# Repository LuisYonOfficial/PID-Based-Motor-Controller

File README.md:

# PID-Based-Motor-Controller
Feedback controlled 3 phase BLDC motor controller. Hardware and all required files will be hosted here. Repo currently under construction!

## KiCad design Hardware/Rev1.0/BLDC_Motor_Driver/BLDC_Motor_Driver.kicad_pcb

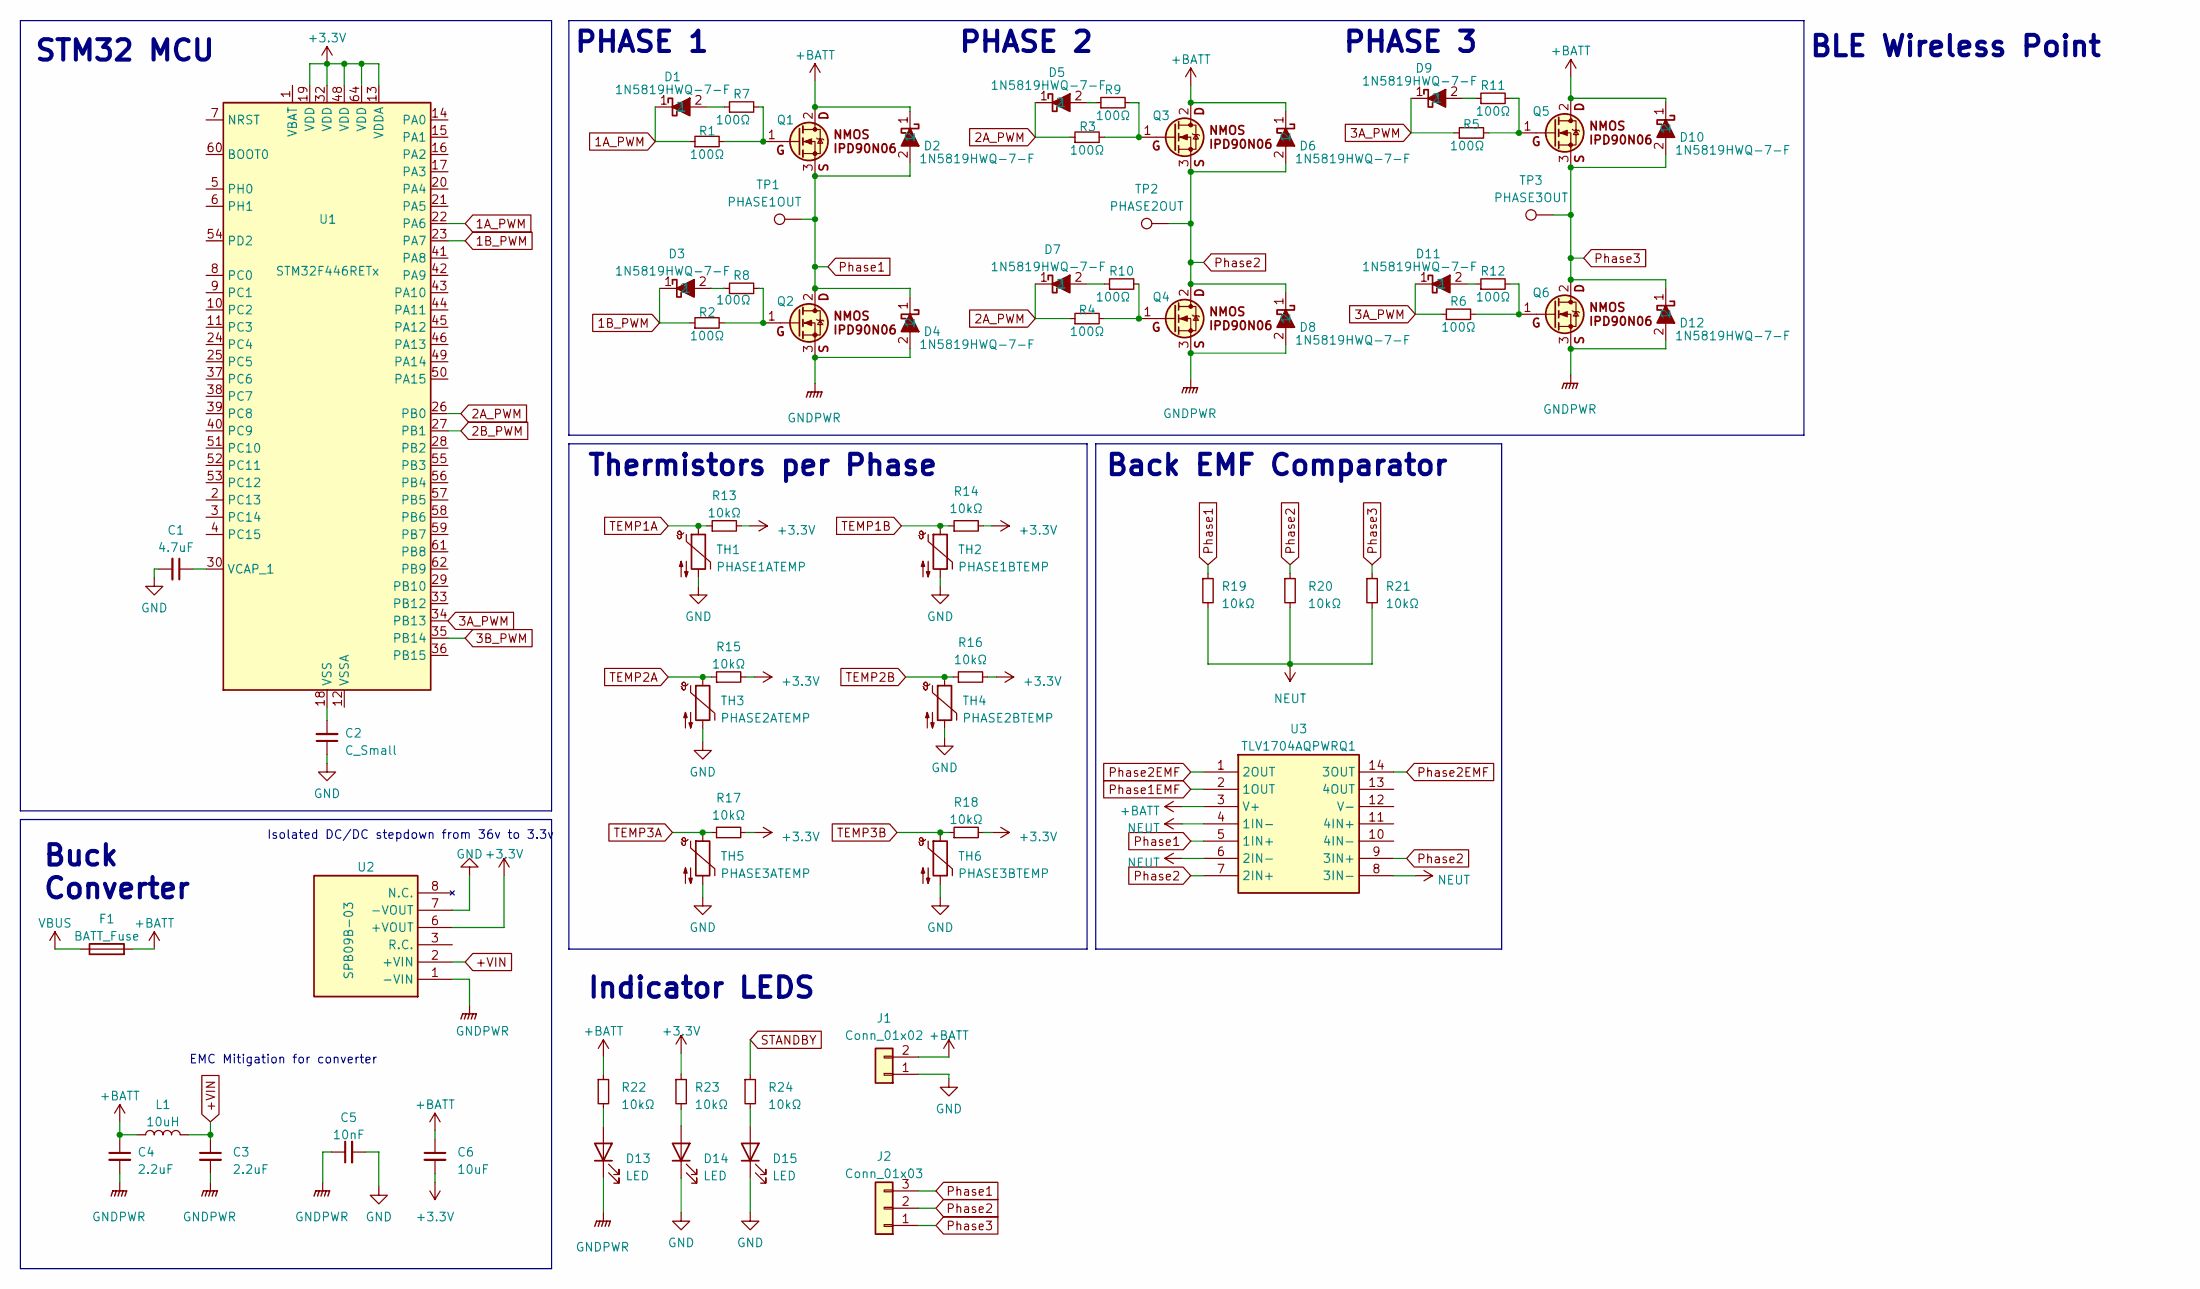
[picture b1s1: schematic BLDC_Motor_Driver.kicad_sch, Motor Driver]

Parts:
C1: 4.7uF; C_0603_1608Metric
C2: C_Small; C_0603_1608Metric
C3, C4: 2.2uF; C_0603_1608Metric
C5: 10nF; C_0603_1608Metric
C6: 10uF; C_0603_1608Metric
D1, D2, D3, D4, D5, D6, D7, D8, D9, D10, D11, D12: 1N5819HWQ-7-F; SOD3716X145N; Mouser Part Number 621-1N5819HWQ-7-F
D13, D14, D15: LED; LED_0603_1608Metric
F1: BATT_Fuse; 3557-2
J1: Conn_01x02
J2: Conn_01x03
L1: 10uH; SRP06152R2K
Q1, Q2, Q3, Q4, Q5, Q6: IPD90N06S4L03ATMA2; IPD90N06S4L03
R1, R2, R3, R4, R5, R6, R7, R8, R9, R10, R11, R12: 100Ω; R_0603_1608Metric
R13, R14, R15, R16, R17, R18, R19, R20, R21, R22, R23, R24: 10kΩ; R_0603_1608Metric
TH1: PHASE1ATEMP; R_0603_1608Metric
TH2: PHASE1BTEMP; R_0603_1608Metric
TH3: PHASE2ATEMP; R_0603_1608Metric
TH4: PHASE2BTEMP; R_0603_1608Metric
TH5: PHASE3ATEMP; R_0603_1608Metric
TH6: PHASE3BTEMP; R_0603_1608Metric
TP1: PHASE1OUT
TP2: PHASE2OUT
TP3: PHASE3OUT
U1: STM32F446RETx; LQFP-64_10x10mm_P0.5mm
U2: SPB09B-03; SPB09B; Mouser Part Number 709-SPB09B-03
U3: TLV1704AQPWRQ1; SOP65P640X120-14N; Mouser Part Number 595-TLV1704AQPWRQ1

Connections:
1A_PWM: D1.1, R1.1, U1.22 (PA6)
1B_PWM: D3.1, R2.1, U1.23 (PA7)
2A_PWM: D5.1, D7.1, R3.1, R4.1, U1.26 (PB0)
2B_PWM: U1.27 (PB1)
3A_PWM: D9.1, D11.1, R5.1, R6.1, U1.34 (PB13)
3B_PWM: U1.35 (PB14)
+3.3V: C6.2, R13.2, R14.2, R15.2, R16.2, R17.2, R18.2, R23.1, U1.13 (VDDA), U1.19 (VDD), U1.32 (VDD), U1.48 (VDD), U1.64 (VDD), U2.6 (+VOUT)
+BATT: C4.1, C6.1, D2.1, D6.1, D10.1, F1.2, J1.2, L1.1, Q1.2, Q3.2, Q5.2, R22.1, U3.3 (V+)
+VIN: C3.1, L1.2, U2.2 (+VIN)
GND: C1.2, C2.1, C5.2, D14.1 (K), D15.1 (K), J1.1, TH1.2, TH2.2, TH3.2, TH4.2, TH5.2, TH6.2, U2.7 (-VOUT)
GNDPWR: C3.2, C4.2, C5.1, D4.2, D8.2, D12.2, D13.1 (K), Q2.3, Q4.3, Q6.3, U2.1 (-VIN)
NEUT: R19.2, R20.2, R21.2, U3.4 (1IN-), U3.6 (2IN-), U3.8 (3IN-)
unnamed: C2.2, U1.18 (VSS), U1.31 (VSS), U1.47 (VSS), U1.63 (VSS)
unnamed: D1.2, R7.1
unnamed: D3.2, R8.1
unnamed: D5.2, R9.1
unnamed: D7.2, R10.1
unnamed: D9.2, R11.1
unnamed: D11.2, R12.1
unnamed: D13.2 (A), R22.2
unnamed: D14.2 (A), R23.2
unnamed: D15.2 (A), R24.2
unnamed: Q1.1, R1.2, R7.2
unnamed: Q2.1, R2.2, R8.2
unnamed: Q3.1, R3.2, R9.2
unnamed: Q4.1, R4.2, R10.2
unnamed: Q5.1, R5.2, R11.2
unnamed: Q6.1, R6.2, R12.2
unnamed: C1.1, U1.30 (VCAP_1)
Phase1: D2.2, D4.1, J2.3, Q1.3, Q2.2, R19.1, TP1.1, U3.5 (1IN+)
Phase1EMF: U3.2 (1OUT)
Phase2: D6.2, D8.1, J2.2, Q3.3, Q4.2, R20.1, TP2.1, U3.7 (2IN+), U3.9 (3IN+)
Phase2EMF: U3.1 (2OUT), U3.14 (3OUT)
Phase3: D10.2, D12.1, J2.1, Q5.3, Q6.2, R21.1, TP3.1
STANDBY: R24.1
TEMP1A: R13.1, TH1.1
TEMP1B: R14.1, TH2.1
TEMP2A: R15.1, TH3.1
TEMP2B: R16.1, TH4.1
TEMP3A: R17.1, TH5.1
TEMP3B: R18.1, TH6.1
VBUS: F1.1

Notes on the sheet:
Buck Converter
Back EMF Comparator
PHASE 2
Isolated DC/DC stepdown from 36v to 3.3v
PHASE 3
BLE Wireless Point
PHASE 1
EMC Mitigation for converter
STM32 MCU
Thermistors per Phase
Indicator LEDS

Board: 2 copper layers, 62 parts (0 on the bottom side), 37 nets, no tracks yet.

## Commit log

2023-04-11 General Schematic update (10% done)
    Started general motor controller (open loop no feedback yet). Only on schematic. Values still need to be entered for resistors and the
2023-04-11 Updates to Stages and MCU inputs
    Selected NMOS's and added basis for back EMF
2023-04-12 Added changes to schematic (20% competed)
    Updated datasheets and schematic symbols for the NMOS FETs. Still need to establish resistor values.
2023-04-14 Schematic Updates (MOSFETs)
    Assigned preliminary rlimit values, modified some footprint placements, and fixed a MOSFET misassignment for schematics.
2023-04-17 Started some PCB edits
    Minor PCB layout edits
